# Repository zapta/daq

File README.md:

# Data Acquisition

| :warning: WARNING|
|:---|
| This design is an unverified work in progress (as of May 2023).|

* [Backplane](./backplane/README.md)
* [Proto board](./proto_board/README.md)
* [Controller board](./controller/README.md)
* [Power supply board](./power_supply/README.md)

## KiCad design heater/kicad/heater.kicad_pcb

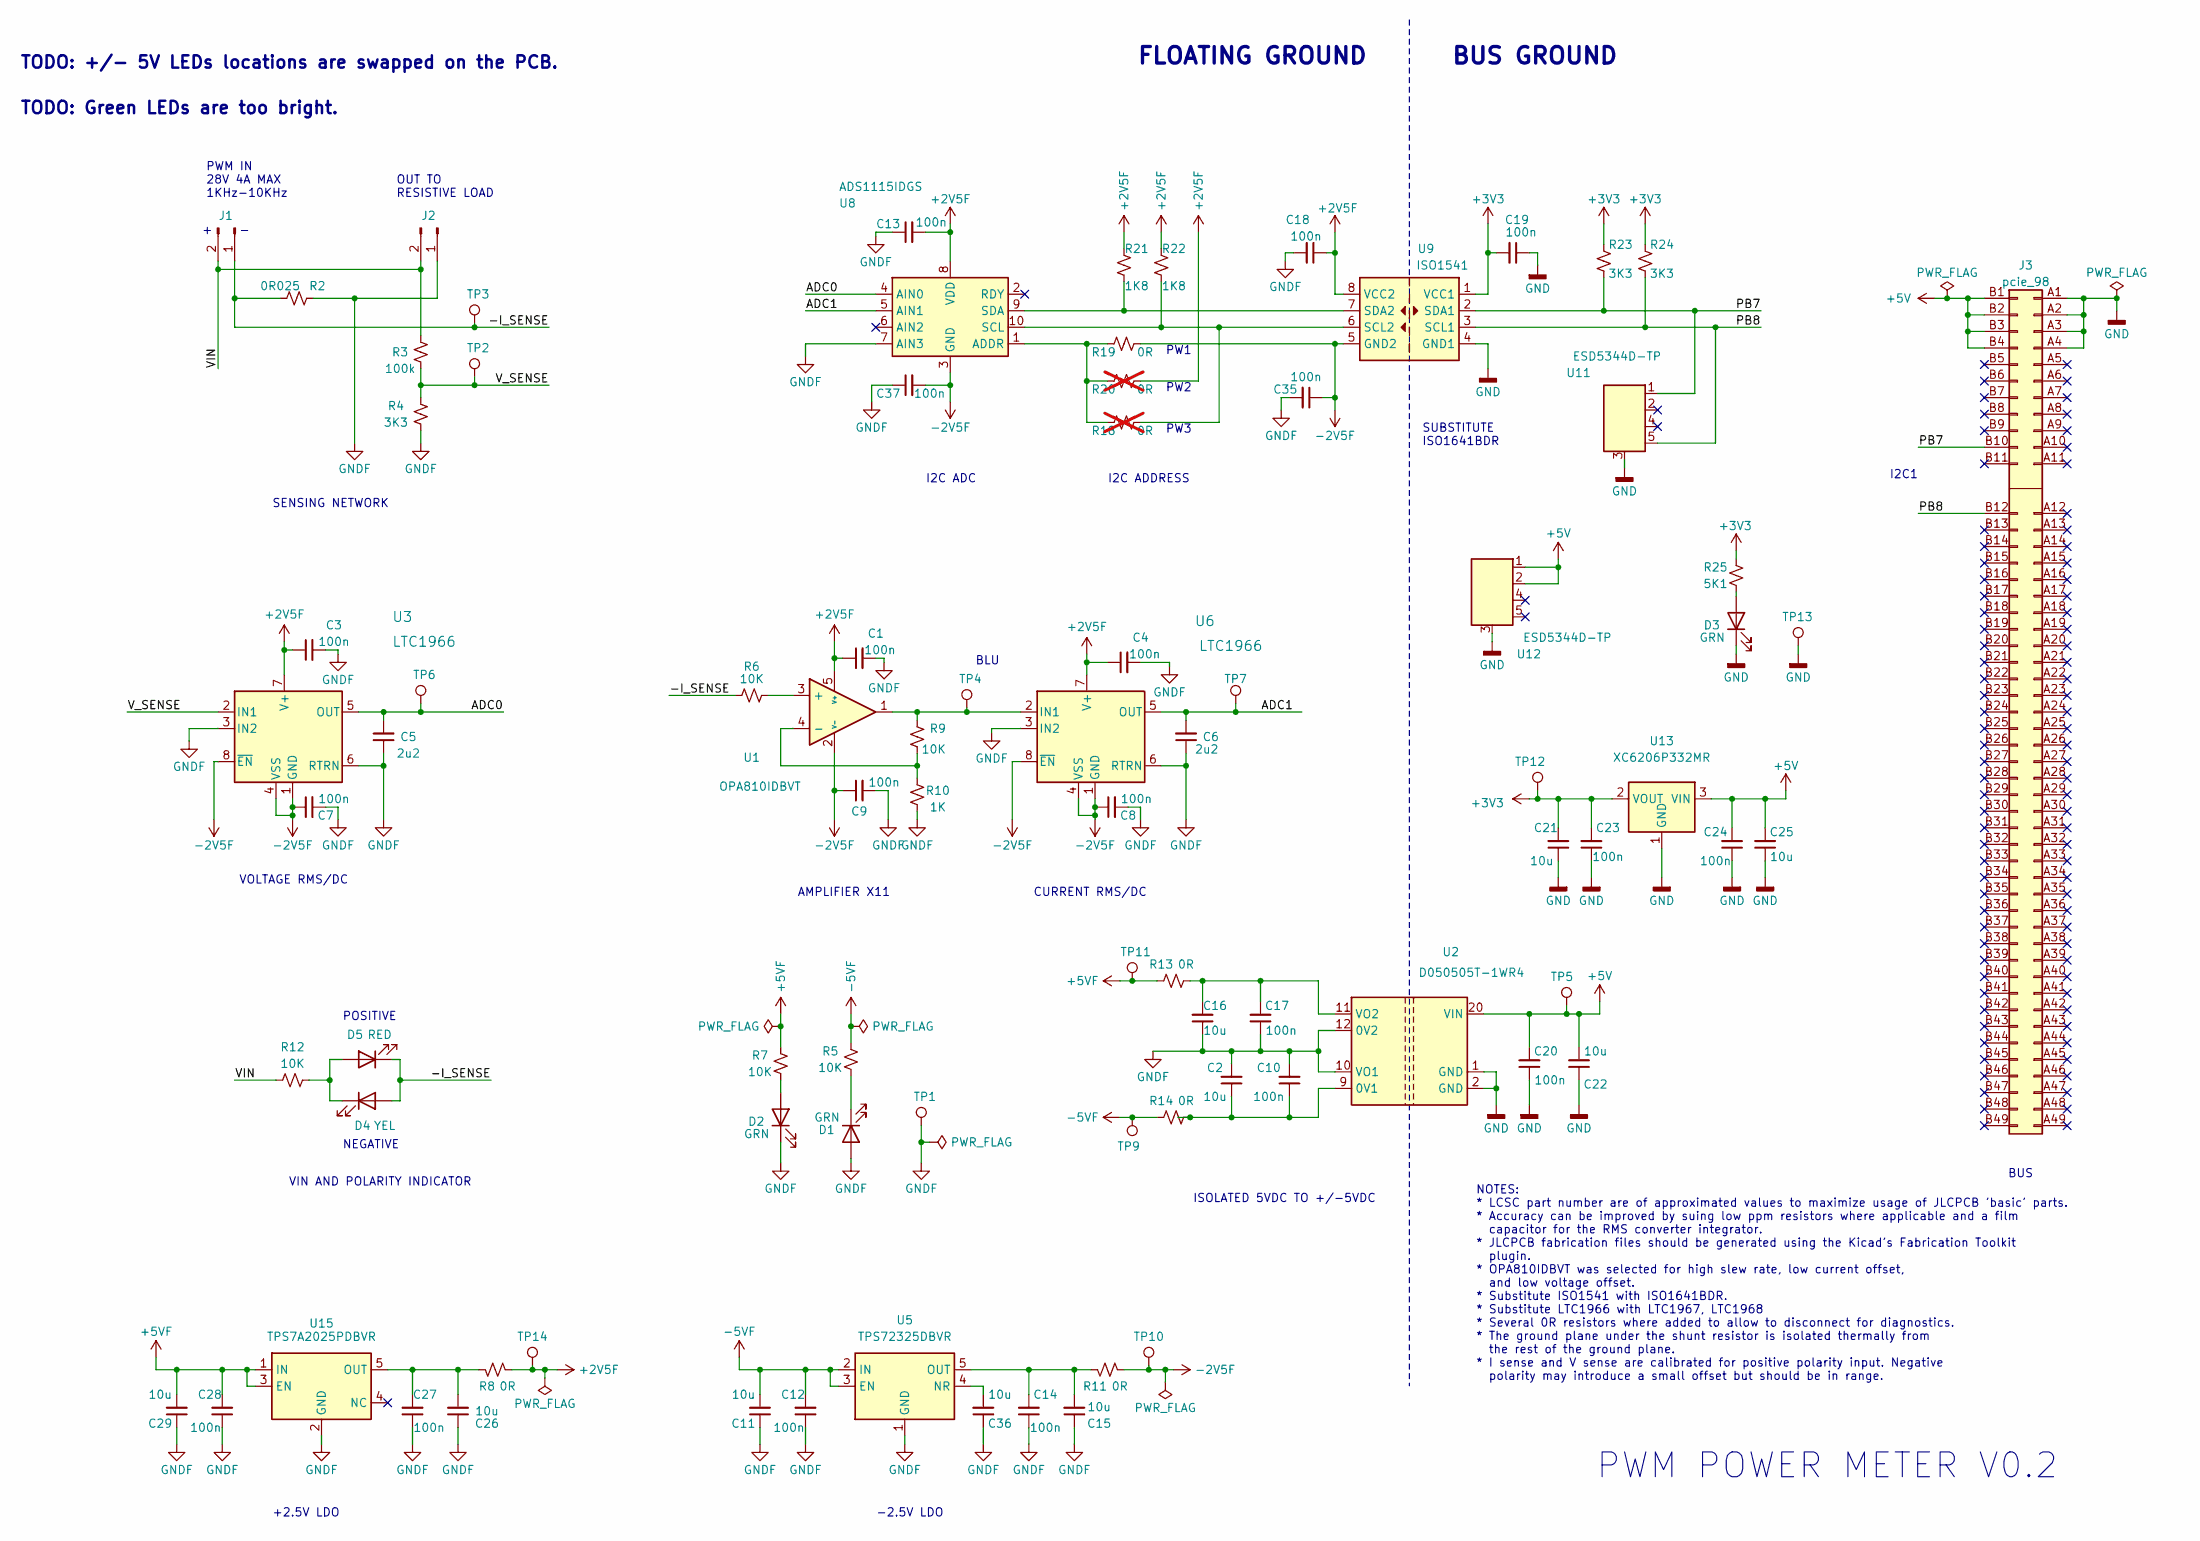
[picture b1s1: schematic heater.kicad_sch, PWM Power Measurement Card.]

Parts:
C1, C3, C4, C7, C8, C9, C10, C12, C13, C14, C17, C18, C19, C20, C23, C24, C27, C28, C35, C37: 100n; C_0402_1005Metric; LCSC C1525
C2, C11, C15, C16, C21, C22, C25, C26, C29, C36: 10u; C_0603_1608Metric; LCSC C19702
C5, C6: 2u2; C_0805_2012Metric; LCSC C377773
D1, D2, D3: GRN; LED_0603_1608Metric; LCSC C72043
D4: YEL; LED_0603_1608Metric; LCSC C72038
D5: RED; LED_0603_1608Metric; LCSC C2286
J1, J2: Conn_01x02_Pin; JST_VH_2_CHINESE; LCSC C2845758
J3: pcie_98; PCIE_98_CARD; LCSC DNP
R2: 0R025; R_2512_6332Metric; LCSC C252687
R3: 100k; R_0402_1005Metric; LCSC C25741
R4: 3K3; R_0402_1005Metric; LCSC C25890
R5, R7: 10K; R_0402_1005Metric
R6, R9, R12: 10K; R_0402_1005Metric; LCSC C25744
R8, R11, R13, R14, R19: 0R; R_0402_1005Metric; LCSC C17168
R10: 1K; R_0402_1005Metric; LCSC C11702
R18, R20: 0R; R_0402_1005Metric; LCSC C17168; not fitted
R21, R22: 1K8; R_0402_1005Metric; LCSC C4109
R23, R24: 3K3; R_0402_1005Metric
R25: 5K1; R_0402_1005Metric
TP1, TP2, TP3, TP4, TP5, TP6, TP7, TP9, TP10, TP11, TP12, TP13, TP14: TestPoint; Test_Pad; LCSC DNP
U1: OPA810IDBVT; TSOT-23-5; LCSC C4154868
U2: D050505T-1WR4; LCSC C2692185
U3, U6: LTC1966; MSOP-8_3x3mm_P0.65mm; LCSC C462623
U5: TPS72325DBVR; SOT-23-5; LCSC C69932
U8: ADS1115IDGS; VSSOP-10_3x3mm_P0.5mm; LCSC C37593
U9: ISO1541; SOIC-8_3.9x4.9mm_P1.27mm; JLCRotOffset 270
U11, U12: ESD5344D-TP; Diodes_UDFN-10_1.0x2.5mm_P0.5mm; LCSC C2841840
U13: XC6206P332MR; SOT-23-3; LCSC C5446
U15: TPS7A2025PDBVR; SOT-23-5; LCSC C2869949

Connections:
+2V5F: C1.1, C3.1, C4.1, C13.2, C18.1, R8.1, R20.2, R21.2, R22.2, TP14.1, U1.5 (V+), U3.7 (V+), U6.7 (V+), U8.8 (VDD), U9.8 (VCC2)
+3V3: C19.2, C21.2, C23.2, R23.2, R24.2, R25.1, TP12.1, U9.1 (VCC1), U13.2 (VOUT)
+5V: C20.2, C22.2, C24.2, C25.2, J3.B1 (Pin_b1), J3.B2 (Pin_b2), J3.B3 (Pin_b3), J3.B4 (Pin_b4), TP5.1, U2.20 (VIN), U12.1 (D1), U12.2 (D2), U13.3 (VIN)
+5VF: C28.2, C29.2, R7.1, R13.2, TP11.1, U15.1 (IN), U15.3 (EN)
-2V5F: C7.1, C8.1, C9.1, C35.1, C37.2, R11.1, R19.2, TP10.1, U1.2 (V-), U3.1 (GND), U3.4 (VSS), U3.8 (~EN), U6.1 (GND), U6.4 (VSS), U6.8 (~EN), U8.3 (GND), U9.5 (GND2)
-5VF: C11.2, C12.2, R5.1, R14.2, TP9.1, U5.2 (IN), U5.3 (EN)
/-I_SENSE: D4.2 (A), D5.1 (K), J1.1, R2.1, R6.1, TP3.1
/ADC0: C5.2, TP6.1, U3.5 (OUT), U8.4 (AIN0)
/ADC1: C6.2, TP7.1, U6.5 (OUT), U8.5 (AIN1)
/PB7: J3.B10 (Pin_b10), R23.1, U9.2 (SDA1), U11.1 (D1)
/PB8: J3.B12 (Pin_b12), R24.1, U9.3 (SCL1), U11.5 (D4)
/VIN: J1.2, J2.2, R3.2, R12.1
/V_SENSE: R3.1, R4.1, TP2.1, U3.2 (IN1)
GND: C19.1, C20.1, C21.1, C22.1, C23.1, C24.1, C25.1, D3.1 (K), J3.A1 (Pin_a1), J3.A2 (Pin_a2), J3.A3 (Pin_a3), J3.A4 (Pin_a4), TP13.1, U2.1 (GND), U2.2 (GND), U9.4 (GND1), U11.3 (GND), U12.3 (GND), U13.1 (GND)
GNDF: C1.2, C2.2, C3.2, C4.2, C5.1, C6.1, C7.2, C8.2, C9.2, C10.2, C11.1, C12.1, C13.1, C14.1, C15.1, C16.1, C17.1, C18.2, C26.1, C27.1, C28.1, C29.1, C35.2, C36.1, C37.1, D1.2 (A), D2.1 (K), J2.1, R2.2, R4.2, R10.1, TP1.1, U2.10 (VO1), U2.12 (0V2), U3.3 (IN2), U3.6 (RTRN), U5.1 (GND), U6.3 (IN2), U6.6 (RTRN), U8.7 (AIN3), U15.2 (GND)
unnamed: D1.1 (K), R5.2
unnamed: D2.2 (A), R7.2
unnamed: D3.2 (A), R25.2
unnamed: D4.1 (K), D5.2 (A), R12.2
unnamed: R6.2, U1.3 (+)
unnamed: R9.2, R10.2, U1.4 (-)
unnamed: C2.1, C10.1, R14.1, U2.9 (0V1)
unnamed: C16.2, C17.2, R13.1, U2.11 (VO2)
unnamed: C36.2, U5.4 (NR)
unnamed: C14.2, C15.2, R11.2, U5.5 (OUT)
unnamed: R9.1, TP4.1, U1.1, U6.2 (IN1)
unnamed: R18.1, R19.1, R20.1, U8.1 (ADDR)
unnamed: R18.2, R22.1, U8.10 (SCL), U9.6 (SCL2)
unnamed: R21.1, U8.9 (SDA), U9.7 (SDA2)
unnamed: C26.2, C27.2, R8.2, U15.5 (OUT)

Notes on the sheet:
PW2
FLOATING GROUND
SENSING NETWORK
OUT TO RESISTIVE LOAD
BUS
TODO: Green LEDs are too bright.
I2C ADDRESS
PWM IN 28V 4A MAX 1KHz-10KHz
NEGATIVE
PW1
-2.5V LDO
AMPLIFIER X11
BLU
POSITIVE
I2C1
+2.5V LDO
PW3
PWM POWER METER V0.2
VIN AND POLARITY INDICATOR
NOTES: * LCSC part number are of approximated values to maximize usage of JLCPCB 'basic' parts. * Accuracy can be improved by suing low ppm resistors where applicable and a film capacitor for the RMS converter integrator. * JLCPCB fabrication files should be generated using the Kicad's Fabrication 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
I2C ADC
SUBSTITUTE ISO1641BDR
VOLTAGE RMS/DC
TODO: +/- 5V LEDs locations are swapped on the PCB.
ISOLATED 5VDC TO +/-5VDC
BUS GROUND
CURRENT RMS/DC

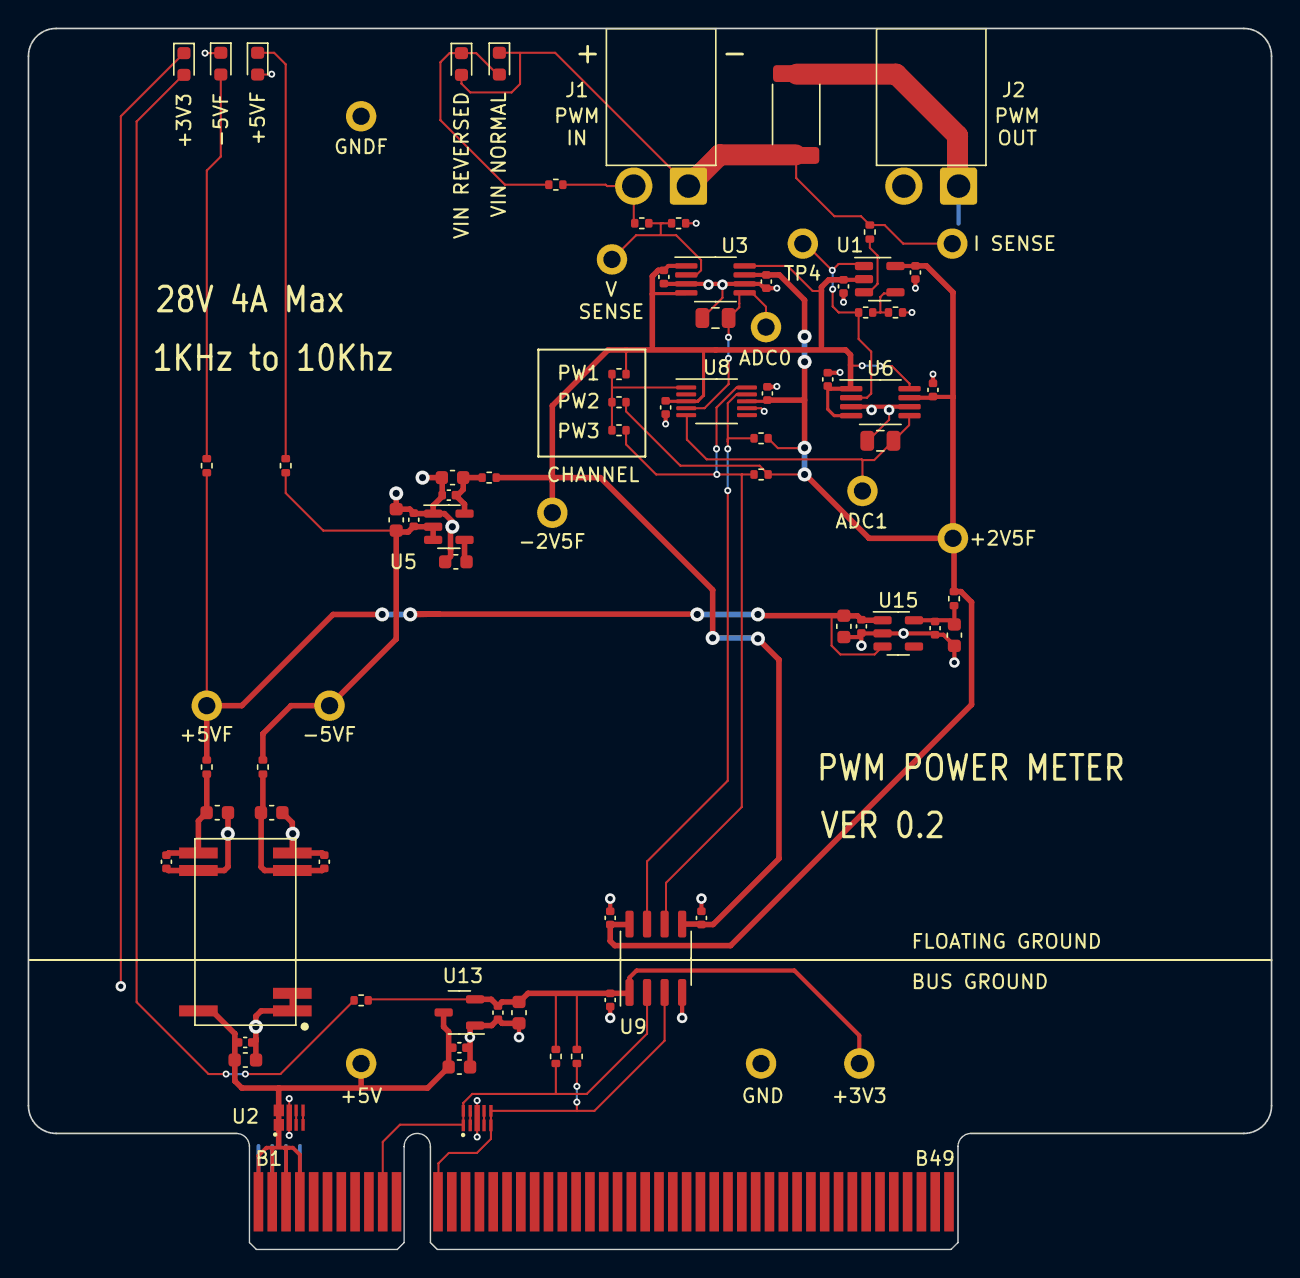
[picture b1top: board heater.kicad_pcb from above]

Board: 2 copper layers, 90.0 x 88.4 mm, 85 parts (0 on the bottom side), 30 nets.

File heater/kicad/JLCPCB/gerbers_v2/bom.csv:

Designator,Footprint,Quantity,Value,LCSC Part #
"C1, C10, C12, C13, C14, C17, C18, C19, C20, C23, C24, C27, C28, C3, C35, C37, C4, C7, C8, C9",0402,20,100n,C1525
"C11, C15, C16, C2, C21, C22, C25, C26, C29, C36",0603,10,10u,C19702
"C5, C6",0805,2,2u2,C377773
"D1, D2, D3",0603,3,GRN,C72043
D4,0603,1,YEL,C72038
D5,0603,1,RED,C2286
"J1, J2",JST_VH_2_CHINESE,2,Conn_01x02_Pin,C2845758
R10,0402,1,1K,C11702
"R11, R13, R14, R19, R8",0402,5,0R,C17168
"R12, R6, R9",0402,3,10K,C25744
R2,2512,1,0R025,C252687
"R21, R22, R23, R24",0402,4,1K8,C4109
"R25, R4",0402,2,3K3,C25890
R3,0402,1,100k,C25741
"R5, R7",0402,2,5K1,C25905
U1,TSOT-23-5,1,OPA810IDBVT,C4154868
"U11, U12",Diodes_UDFN-10_1.0x2.5mm_P0.5mm,2,ESD5344D-TP,C2841840
U13,SOT-23-3,1,XC6206P332MR,C5446
U15,SOT-23-5,1,TPS7A2025PDBVR,C2869949
U2,D050505T-1WR4,1,D050505T-1WR4,C2692185
"U3, U6",MSOP-8_3x3mm_P0.65mm,2,LTC1966,C462623
U5,SOT-23-5,1,TPS72325DBVR,C69932
U8,VSSOP-10_3x3mm_P0.5mm,1,ADS1115IDGS,C37593
U9,SOIC-8_3.9x4.9mm_P1.27mm,1,ISO1541,ISO1541DR

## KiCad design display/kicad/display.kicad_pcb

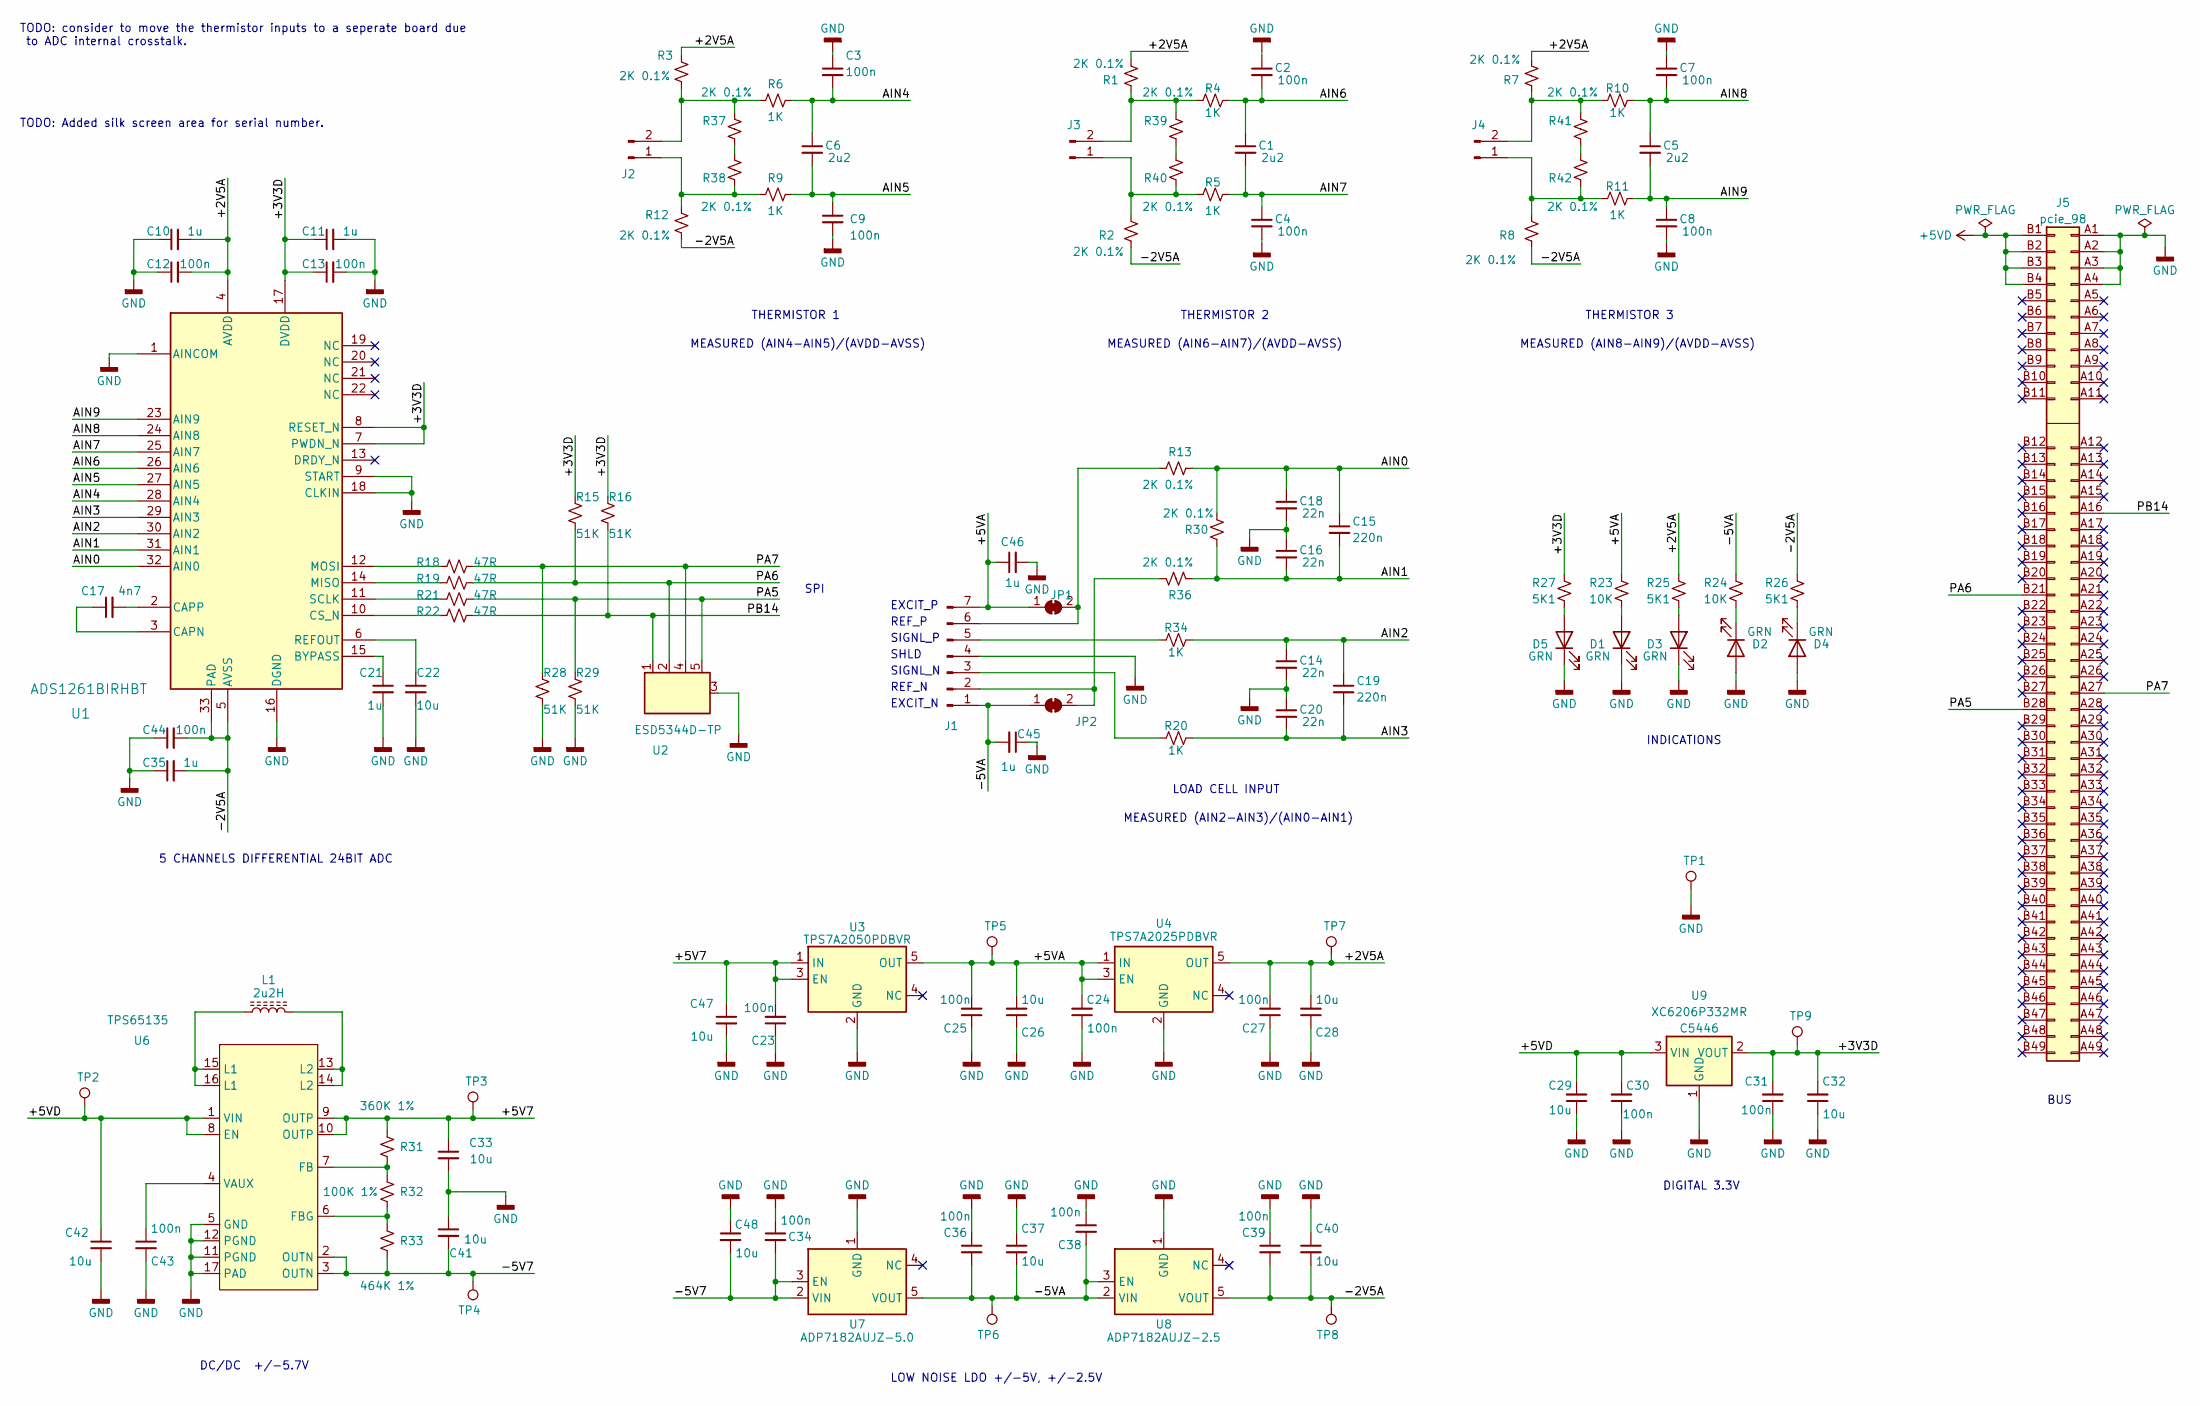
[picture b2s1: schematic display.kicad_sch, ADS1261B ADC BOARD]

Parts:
C1, C5, C6: 2u2; C_0402_1005Metric; LCSC C12530
C2, C3, C4, C7, C8, C9, C12, C13, C23, C24, C25, C27, C30, C31, C34, C36, C38, C39, C43, C44: 100n; C_0402_1005Metric; LCSC C1525
C10, C11, C21, C35, C45, C46: 1u; C_0402_1005Metric; LCSC C52923
C14, C16, C18, C20: 22n; C_0402_1005Metric; LCSC C1532
C15, C19: 220n; C_0402_1005Metric; LCSC C16772
C17: 4n7; C_0402_1005Metric; LCSC C1538
C22, C26, C28, C29, C32, C33, C37, C40, C41, C42, C47, C48: 10u; C_0603_1608Metric; LCSC C19702
D1, D2, D3, D4, D5: GRN; LED_0603_1608Metric; LCSC C72043
J1: Conn_01x07_Pin; connector_7pins_horizontal; LCSC C70896
J2, J3, J4: Conn_01x02_Pin; connector_2pins_horizontal; LCSC C30436
J5: pcie_98; PCIE_98_CARD; LCSC DNP
JP1, JP2: SolderJumper_2_Bridged; SolderJumper-2_P1.3mm_Bridged_Pad1.0x1.5mm; LCSC DNP
L1: 2u2H; Inductor_C329578; LCSC C329578
R1, R2, R3, R7, R8, R12, R13, R30, R36, R37, R38, R39, R40, R41, R42: 2K 0.1%; R_0402_1005Metric; LCSC C852711
R4, R5, R6, R9, R10, R11, R20, R34: 1K; R_0402_1005Metric; LCSC C11702
R15, R16, R28, R29: 51K; R_0402_1005Metric; LCSC C25794
R18, R19, R21, R22: 47R; R_0402_1005Metric; LCSC C25118
R23, R24: 10K; R_0402_1005Metric; LCSC C25744
R25, R26, R27: 5K1; R_0402_1005Metric; LCSC C25905
R31: 360K 1%; R_0402_1005Metric; LCSC C308007
R32: 100K 1%; R_0402_1005Metric; LCSC C25741
R33: 464K 1%; R_0402_1005Metric; LCSC C477740
TP1, TP2, TP3, TP4, TP5, TP6, TP7, TP8, TP9: TestPoint; Test_Pad
U1: ADS1261BIRHBT; RHB0032E; LCSC C2669964
U2: ESD5344D-TP; Diodes_UDFN-10_1.0x2.5mm_P0.5mm; LCSC C2841840
U3: TPS7A2050PDBVR; SOT-23-5; LCSC C2864504
U4: TPS7A2025PDBVR; SOT-23-5; LCSC C2869949
U6: TPS65135; WQFN-16-1EP_3x3mm_P0.5mm_EP1.68x1.68mm_ThermalVias; LCSC C57950
U7: ADP7182AUJZ-5.0; TSOT-23-5; LCSC C514357
U8: ADP7182AUJZ-2.5; TSOT-23-5; LCSC C462196
U9: XC6206P332MR; SOT-23-3; LCSC C5446

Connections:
+5VD: C29.2, C30.2, C42.1, J5.B1 (Pin_b1), J5.B2 (Pin_b2), J5.B3 (Pin_b3), J5.B4 (Pin_b4), TP2.1, U6.1 (VIN), U6.8 (EN), U9.3 (VIN)
/+2V5A: C10.2, C12.2, C27.2, C28.2, R1.2, R3.2, R7.2, R25.1, TP7.1, U1.4 (AVDD), U4.5 (OUT)
/+3V3D: C11.1, C13.1, C31.2, C32.2, R15.2, R16.2, R27.1, TP9.1, U1.7 (PWDN_N), U1.8 (RESET_N), U1.17 (DVDD), U9.2 (VOUT)
/+5V7: C23.2, C33.1, C47.1, R31.1, TP3.1, U3.1 (IN), U3.3 (EN), U6.9 (OUTP), U6.10 (OUTP)
/+5VA: C24.2, C25.2, C26.2, C46.1, J1.7, JP1.1 (A), R23.1, TP5.1, U3.5 (OUT), U4.1 (IN), U4.3 (EN)
/-2V5A: C35.2, C39.2, C40.2, C44.2, R2.1, R8.1, R12.1, R26.1, TP8.1, U1.5 (AVSS), U1.33 (PAD), U8.5 (VOUT)
/-5V7: C34.2, C41.2, C48.2, R33.2, TP4.1, U6.2 (OUTN), U6.3 (OUTN), U7.2 (VIN), U7.3 (EN)
/-5VA: C36.2, C37.2, C38.2, C45.2, J1.1, JP2.1 (A), R24.1, TP6.1, U7.5 (VOUT), U8.2 (VIN), U8.3 (EN)
/AIN0: C15.1, C18.1, R13.1, R30.2, U1.32 (AIN0)
/AIN1: C15.2, C16.2, R30.1, R36.1, U1.31 (AIN1)
/AIN2: C14.1, C19.1, R34.2, U1.30 (AIN2)
/AIN3: C19.2, C20.2, R20.2, U1.29 (AIN3)
/AIN4: C3.2, C6.1, R6.2, U1.28 (AIN4)
/AIN5: C6.2, C9.1, R9.2, U1.27 (AIN5)
/AIN6: C1.1, C2.2, R4.2, U1.26 (AIN6)
/AIN7: C1.2, C4.1, R5.2, U1.25 (AIN7)
/AIN8: C5.1, C7.2, R10.2, U1.24 (AIN8)
/AIN9: C5.2, C8.1, R11.2, U1.23 (AIN9)
/PA5: J5.B28 (Pin_b28), R21.1, R29.2, U2.5 (D4)
/PA6: J5.B21 (Pin_b21), R15.1, R19.1, U2.2 (D2)
/PA7: J5.A27 (Pin_a27), R18.1, R28.2, U2.4 (D3)
/PB14: J5.A16 (Pin_a16), R16.1, R22.1, U2.1 (D1)
GND: C2.1, C3.1, C4.2, C7.1, C8.2, C9.2, C10.1, C11.2, C12.1, C13.2, C14.2, C16.1, C18.2, C20.1, C21.2, C22.2, C23.1, C24.1, C25.1, C26.1, C27.1, C28.1, C29.1, C30.1, C31.1, C32.1, C33.2, C34.1, C35.1, C36.1, C37.1, C38.1, C39.1, C40.1, C41.1, C42.2, C43.2, C44.1, C45.1, C46.2, C47.2, C48.1, D1.1 (K), D2.2 (A), D3.1 (K), D4.2 (A), D5.1 (K), J1.4, J5.A1 (Pin_a1), J5.A2 (Pin_a2), J5.A3 (Pin_a3), J5.A4 (Pin_a4), R28.1, R29.1, TP1.1, U1.1 (AINCOM), U1.9 (START), U1.16 (DGND), U1.18 (CLKIN), U2.3 (GND), U3.2 (GND), U4.2 (GND), U6.5 (GND), U6.11 (PGND), U6.12 (PGND), U6.17 (PAD), U7.1 (GND), U8.1 (GND), U9.1 (GND)
unnamed: D1.2 (A), R23.2
unnamed: D2.1 (K), R24.2
unnamed: D3.2 (A), R25.2
unnamed: D4.1 (K), R26.2
unnamed: D5.2 (A), R27.2
unnamed: J1.2, JP2.2 (B), R36.2
unnamed: J1.3, R20.1
unnamed: J1.5, R34.1
unnamed: J1.6, JP1.2 (B), R13.2
unnamed: J2.1, R9.1, R12.2, R38.1
unnamed: J2.2, R3.1, R6.1, R37.2
unnamed: J3.1, R2.2, R5.1, R40.1
unnamed: J3.2, R1.1, R4.1, R39.2
unnamed: J4.1, R8.2, R11.1, R42.1
unnamed: J4.2, R7.1, R10.1, R41.2
unnamed: L1.1, U6.15 (L1), U6.16 (L1)
unnamed: L1.2, U6.13 (L2), U6.14 (L2)
unnamed: R37.1, R38.2
unnamed: R39.1, R40.2
unnamed: R41.1, R42.2
unnamed: C21.1, U1.15 (BYPASS)
unnamed: C17.1, U1.3 (CAPN)
unnamed: C17.2, U1.2 (CAPP)
unnamed: R22.2, U1.10 (CS_N)
unnamed: R19.2, U1.14 (MISO)
unnamed: R18.2, U1.12 (MOSI)
unnamed: C22.1, U1.6 (REFOUT)
unnamed: R21.2, U1.11 (SCLK)
unnamed: R31.2, R32.1, U6.7 (FB)
unnamed: R32.2, R33.1, U6.6 (FBG)
unnamed: C43.1, U6.4 (VAUX)

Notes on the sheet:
TODO: consider to move the thermistor inputs to a seperate board due to ADC internal crosstalk.
SIGNL_N
REF_N
BUS
THERMISTOR 3
SHLD
EXCIT_N
MEASURED (AIN4-AIN5)/(AVDD-AVSS)
SPI
MEASURED (AIN2-AIN3)/(AIN0-AIN1)
INDICATIONS
THERMISTOR 1
MEASURED (AIN6-AIN7)/(AVDD-AVSS)
THERMISTOR 2
MEASURED (AIN8-AIN9)/(AVDD-AVSS)
5 CHANNELS DIFFERENTIAL 24BIT ADC
SIGNL_P
TODO: Added silk screen area for serial number.
DIGITAL 3.3V
LOAD CELL INPUT
REF_P
EXCIT_P
DC/DC +/-5.7V
LOW NOISE LDO +/-5V, +/-2.5V

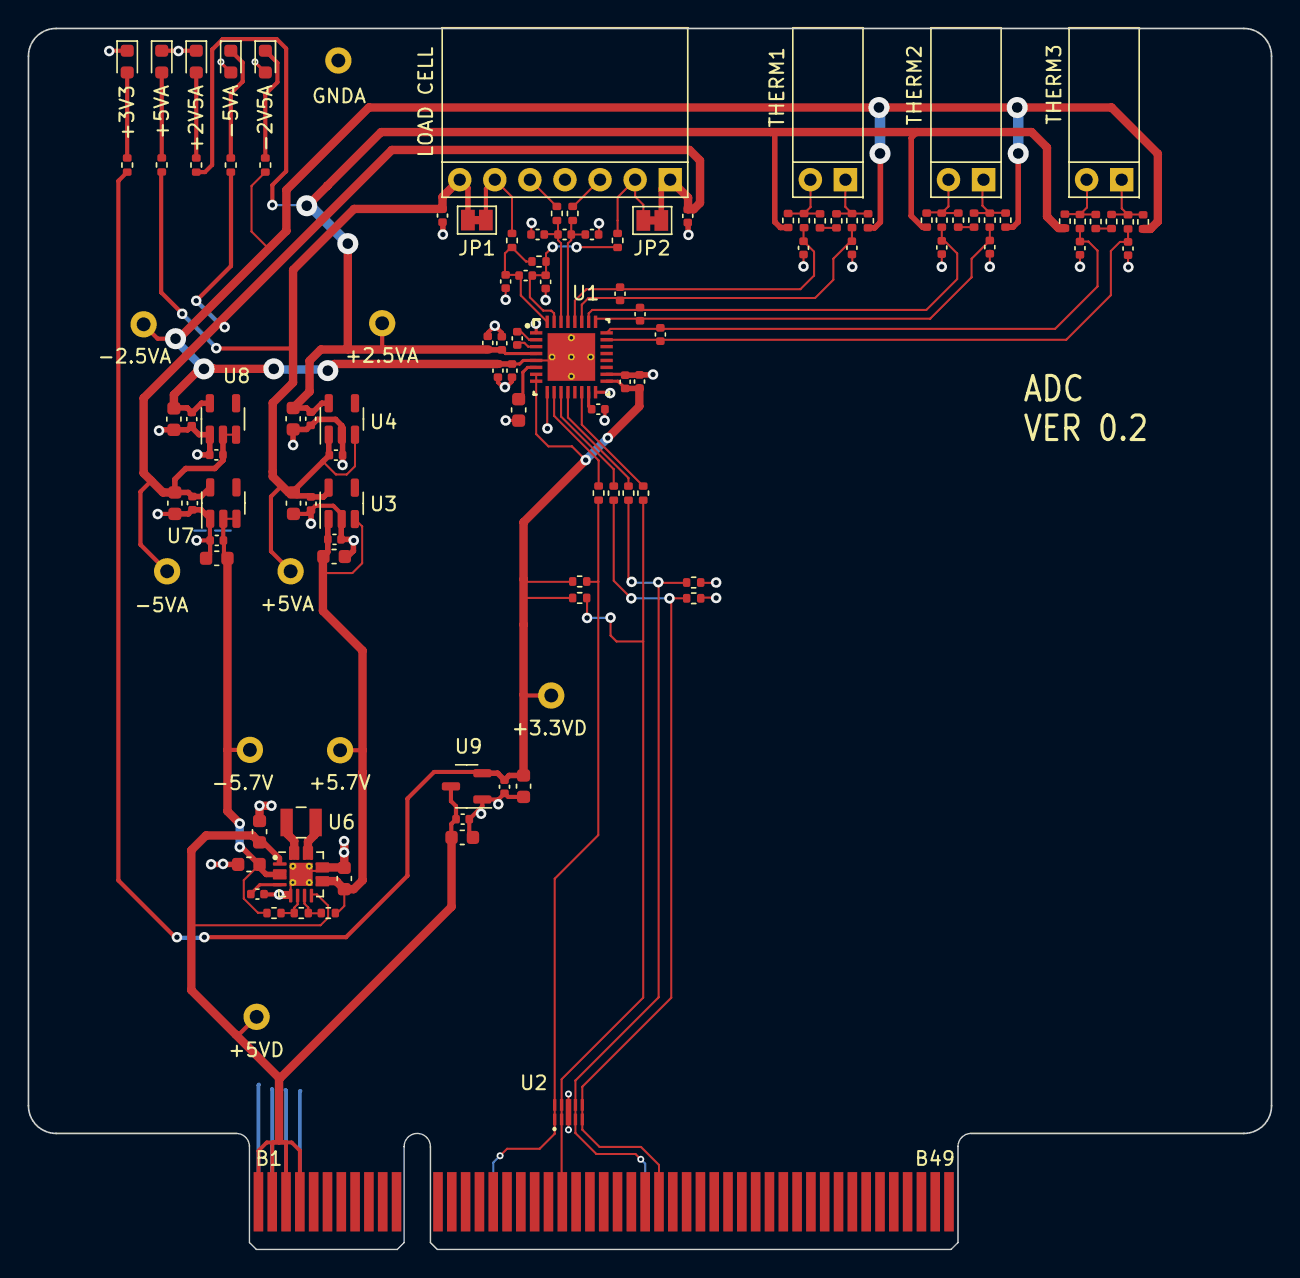
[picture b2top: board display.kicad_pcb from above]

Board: 2 copper layers, 90.0 x 88.4 mm, 117 parts (0 on the bottom side), 54 nets.

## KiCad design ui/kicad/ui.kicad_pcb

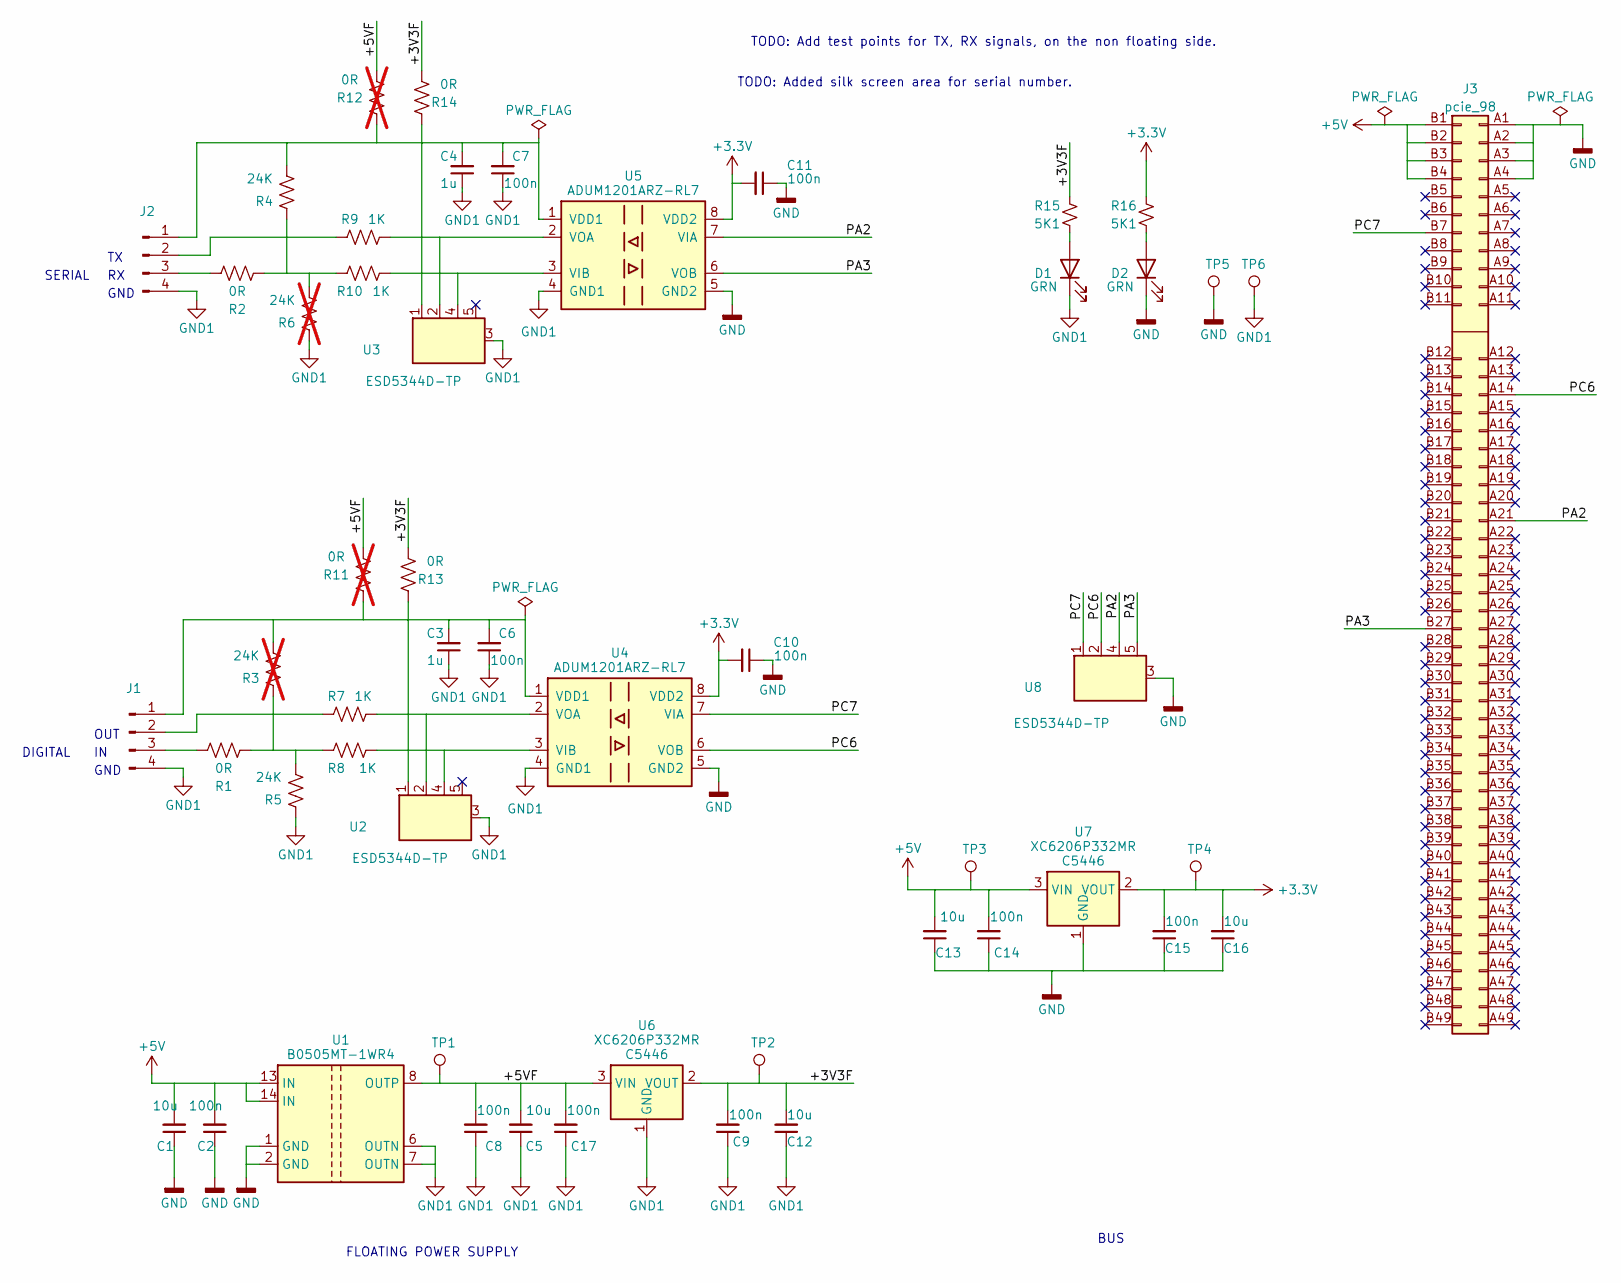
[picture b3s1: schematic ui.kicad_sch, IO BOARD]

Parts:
C1, C5, C12, C13, C16: 10u; C_0603_1608Metric_Pad1.08x0.95mm_HandSolder; LCSC C96446
C2, C6, C7, C8, C9, C10, C11, C14, C15, C17: 100n; C_0603_1608Metric_Pad1.08x0.95mm_HandSolder; LCSC C14663
C3, C4: 1u; C_0603_1608Metric_Pad1.08x0.95mm_HandSolder; LCSC C15849
D1, D2: GRN; LED_0603_1608Metric; LCSC C72043
J1, J2: Conn_01x04_Pin; connector_4pins_horizontal; LCSC C31753
J3: pcie_98; PCIE_98_CARD; LCSC DNP
R1, R2, R13, R14: 0R; R_0603_1608Metric_Pad0.98x0.95mm_HandSolder; LCSC C21189
R3, R6: 24K; R_0603_1608Metric_Pad0.98x0.95mm_HandSolder; LCSC C23352; not fitted
R4, R5: 24K; R_0603_1608Metric_Pad0.98x0.95mm_HandSolder; LCSC C23352
R7, R8, R9, R10: 1K; R_0603_1608Metric_Pad0.98x0.95mm_HandSolder; LCSC C21190
R11, R12: 0R; R_0603_1608Metric_Pad0.98x0.95mm_HandSolder; LCSC C21189; not fitted
R15, R16: 5K1; R_0603_1608Metric_Pad0.98x0.95mm_HandSolder; LCSC C23186
TP1, TP2, TP3, TP4, TP5, TP6: TestPoint; Test_Pad; LCSC DNP
U1: B0505MT-1WR4; Converter_DCDC; LCSC C919693
U2, U3, U8: ESD5344D-TP; Duides_UDFN-10_1.0x2.5mm_P0.5mm; LCSC C2841840
U4, U5: ADUM1201ARZ-RL7; SOIC-8_3.9x4.9mm_P1.27mm; LCSC C9669
U6, U7: XC6206P332MR; SOT-23-3; LCSC C5446

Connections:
+3.3V: C10.2, C11.2, C15.2, C16.2, R16.1, TP4.1, U4.8 (VDD2), U5.8 (VDD2), U7.2 (VOUT)
+5V: C1.2, C2.2, C13.2, C14.2, J3.B1 (Pin_b1), J3.B2 (Pin_b2), J3.B3 (Pin_b3), J3.B4 (Pin_b4), TP3.1, U1.13 (IN), U1.14 (IN), U7.3 (VIN)
/+3V3F: C9.2, C12.2, R13.2, R14.2, R15.1, TP2.1, U6.2 (VOUT)
/+5VF: C5.2, C8.2, C17.2, R11.2, R12.2, TP1.1, U1.8 (OUTP), U6.3 (VIN)
/PA2: J3.A21 (Pin_a21), U5.7 (VIA), U8.4 (D3)
/PA3: J3.B27 (Pin_b27), U5.6 (VOB), U8.5 (D4)
/PC6: J3.A14 (Pin_a14), U4.6 (VOB), U8.2 (D2)
/PC7: J3.B7 (Pin_b7), U4.7 (VIA), U8.1 (D1)
GND: C1.1, C2.1, C10.1, C11.1, C13.1, C14.1, C15.1, C16.1, D2.1 (K), J3.A1 (Pin_a1), J3.A2 (Pin_a2), J3.A3 (Pin_a3), J3.A4 (Pin_a4), TP5.1, U1.1 (GND), U1.2 (GND), U4.5 (GND2), U5.5 (GND2), U7.1 (GND), U8.3 (GND)
GND1: C3.1, C4.1, C5.1, C6.1, C7.1, C8.1, C9.1, C12.1, C17.1, D1.1 (K), J1.4, J2.4, R5.1, R6.1, TP6.1, U1.6 (OUTN), U1.7 (OUTN), U2.3 (GND), U3.3 (GND), U4.4 (GND1), U5.4 (GND1), U6.1 (GND)
unnamed: D1.2 (A), R15.2
unnamed: D2.2 (A), R16.2
unnamed: C3.2, C6.2, J1.1, R3.2, R11.1, R13.1, U2.1 (D1), U4.1 (VDD1)
unnamed: J1.2, R7.1
unnamed: J1.3, R1.2
unnamed: C4.2, C7.2, J2.1, R4.2, R12.1, R14.1, U3.1 (D1), U5.1 (VDD1)
unnamed: J2.2, R9.1
unnamed: J2.3, R2.2
unnamed: R1.1, R3.1, R5.2, R8.1
unnamed: R2.1, R4.1, R6.2, R10.1
unnamed: R7.2, U2.2 (D2), U4.2 (VOA)
unnamed: R8.2, U2.4 (D3), U4.3 (VIB)
unnamed: R9.2, U3.2 (D2), U5.2 (VOA)
unnamed: R10.2, U3.4 (D3), U5.3 (VIB)

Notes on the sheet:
OUT
BUS
FLOATING POWER SUPPLY
TODO: Added silk screen area for serial number.
DIGITAL
TODO: Add test points for TX, RX signals, on the non floating side.
GND
SERIAL

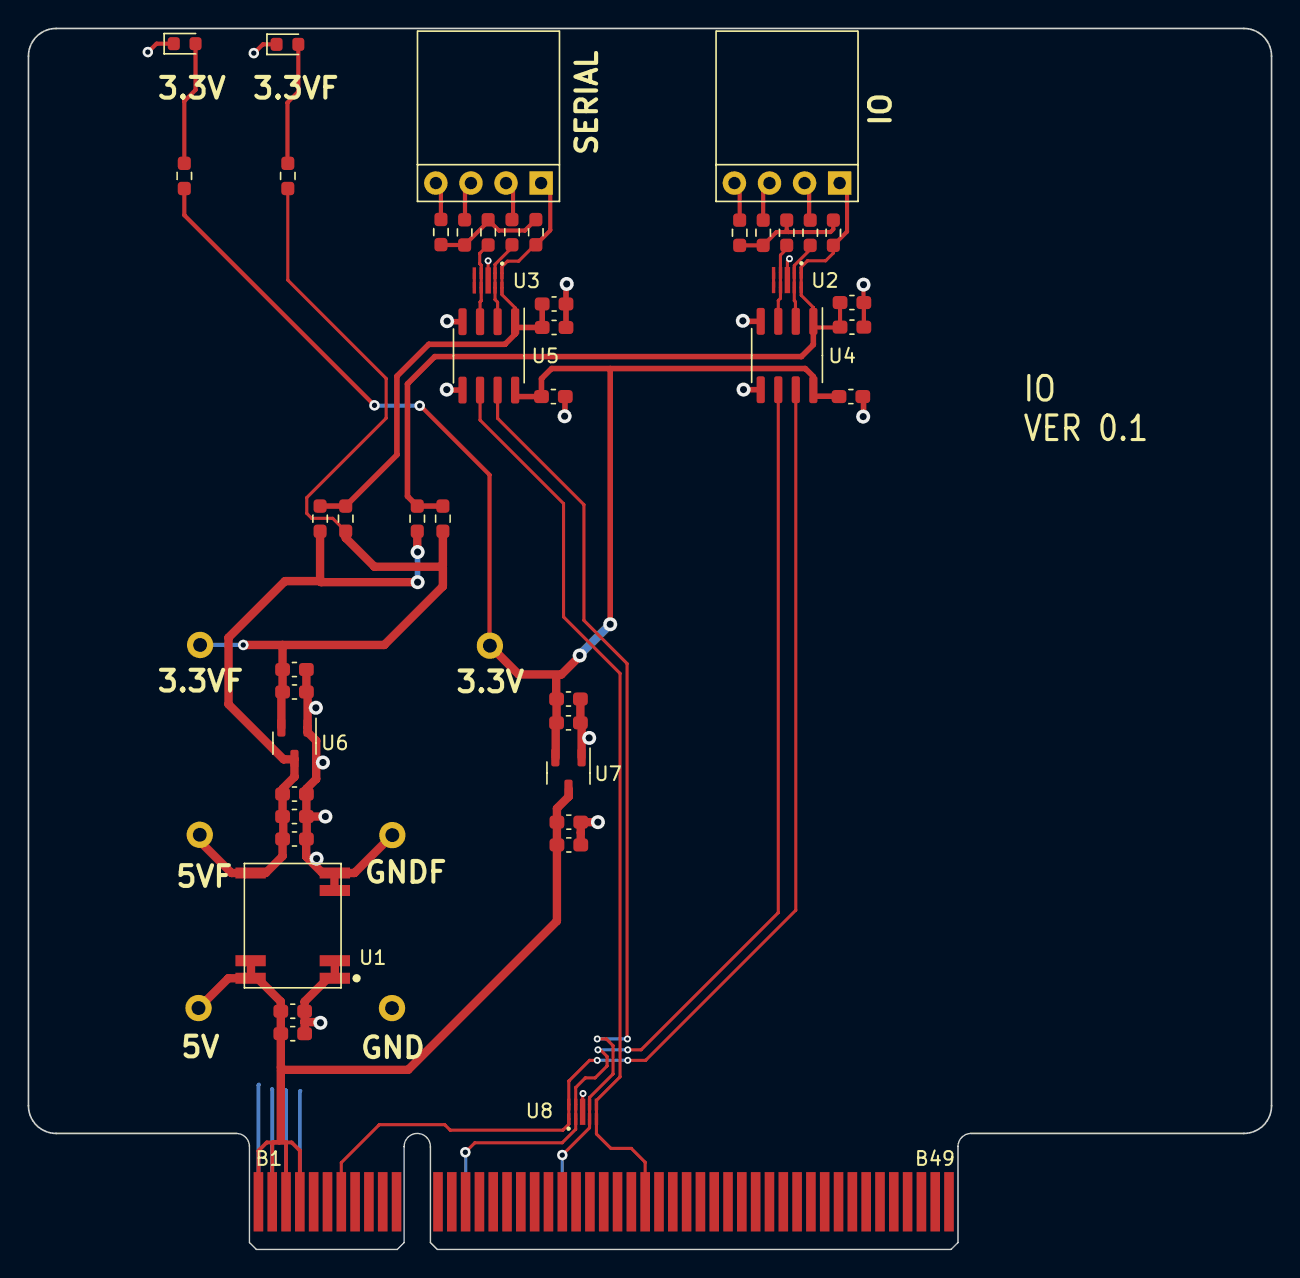
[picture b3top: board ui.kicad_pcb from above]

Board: 2 copper layers, 90.0 x 88.4 mm, 52 parts (0 on the bottom side), 24 nets.
